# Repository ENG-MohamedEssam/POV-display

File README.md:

# POV-display
## Abstract
#### A POV (persistence of vision) display clock is a type of electronic display that uses LEDs to create the illusion of a moving image. In this case, it uses LEDs to represent an analog clock.

#### The system uses an Atmega32 microcontroller, which is a popular choice for embedded systems due to its low power consumption, high processing power and large number of I/O pins.

#### The driver code is responsible for controlling the LEDs, which are connected to the microcontroller's I/O pins. This code is responsible for turning the LEDs on and off at the appropriate times to create the illusion of a moving clock hand.

#### The algorithm is responsible for calculating the position of the clock hands based on the current time. It uses a combination of math and timing functions to determine the position of the hands and then sends the corresponding commands to the driver code to control the LEDs.

#### The project was developed by a team, and it's likely that the team divided the work and each member was responsible for a different part of the project. With this project, the team was able to demonstrate the ability to design and implement a complete embedded systems project, including writing code for both the microcontroller and the algorithm, as well as debugging and testing the system.

### The following is an image of the hardware system.

### You can find a preview of the project using the following link
[POV-Display-Preview](https://drive.google.com/drive/u/0/folders/128i1z9-Xx1qVnHIgvfxdt_CPARsultIw)

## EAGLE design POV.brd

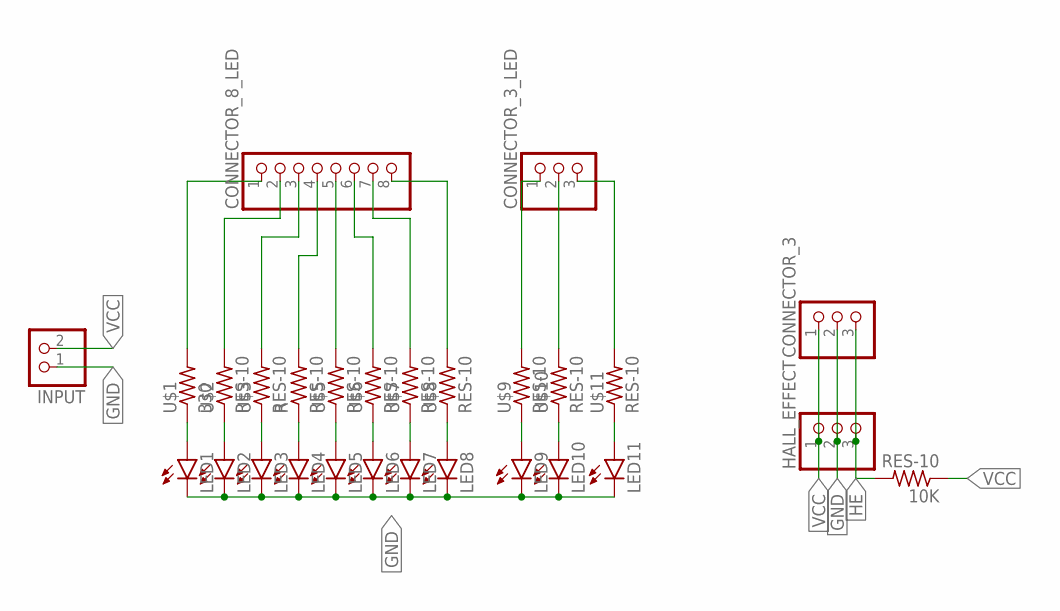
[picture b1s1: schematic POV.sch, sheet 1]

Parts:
10K: RES-10; 0207/10
CONNECTOR_3, CONNECTOR_3_LED: PINHD-1X3; 1X03
CONNECTOR_8_LED: PINHD-1X8; 1X08
HALL_EFFECT: PINHD-1X3; 1X03
INPUT: PINHD-1X2; 1X02
LED1, LED2, LED3, LED4, LED5, LED6, LED7, LED8, LED9, LED10, LED11: LED5MM
R: RES-10; 0207/10
U$1: 330; 0207/10
U$2, U$3, U$5, U$6, U$7, U$8, U$9, U$10, U$11: RES-10; 0207/10

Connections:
GND: CONNECTOR_3.2, HALL_EFFECT.2, INPUT.1, LED1.K (C), LED2.K (C), LED3.K (C), LED4.K (C), LED5.K (C), LED6.K (C), LED7.K (C), LED8.K (C), LED9.K (C), LED10.K (C), LED11.K (C); also elsewhere on the board
HE: 10K.2, CONNECTOR_3.3, HALL_EFFECT.3
unnamed: LED1.A, U$1.1
unnamed: LED2.A, U$2.1
unnamed: LED3.A, U$3.1
unnamed: LED4.A, R.1
unnamed: LED5.A, U$5.1
unnamed: LED6.A, U$6.1
unnamed: LED7.A, U$7.1
unnamed: LED8.A, U$8.1
unnamed: LED9.A, U$9.1
unnamed: LED10.A, U$10.1
unnamed: LED11.A, U$11.1
unnamed: CONNECTOR_8_LED.1, U$1.2
unnamed: CONNECTOR_8_LED.2, U$2.2
unnamed: CONNECTOR_8_LED.3, U$3.2
unnamed: CONNECTOR_8_LED.4, R.2
unnamed: CONNECTOR_8_LED.5, U$5.2
unnamed: CONNECTOR_8_LED.6, U$6.2
unnamed: CONNECTOR_8_LED.7, U$7.2
unnamed: CONNECTOR_8_LED.8, U$8.2
unnamed: CONNECTOR_3_LED.1, U$9.2
unnamed: CONNECTOR_3_LED.2, U$10.2
unnamed: CONNECTOR_3_LED.3, U$11.2
VCC: 10K.1, CONNECTOR_3.1, HALL_EFFECT.1, INPUT.2; also elsewhere on the board

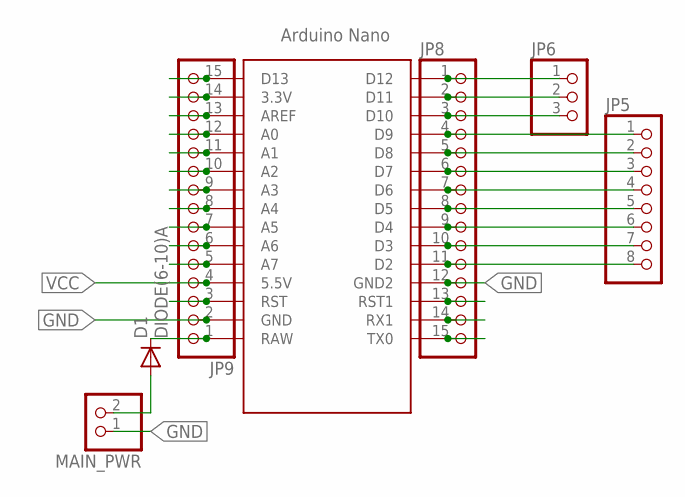
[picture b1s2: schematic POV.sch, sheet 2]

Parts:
D1: DIODE(6-10)A; DO201-15
JP5: PINHD-1X8; 1X08
JP6: PINHD-1X3; 1X03
JP8, JP9: PINHD-1X15; 1X15
MAIN_PWR: PINHD-1X2; 1X02
U$12: ARDUINO_NANO; NANO

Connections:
GND: JP8.12, JP9.2, MAIN_PWR.1, U$12.GND, U$12.GND1 (GND2); also elsewhere on the board
unnamed: JP9.14, U$12.3.3V
unnamed: JP9.13, U$12.AREF
unnamed: JP8.15, U$12.TX0
unnamed: JP8.14, U$12.RX1
unnamed: JP8.13, U$12.RST1
unnamed: JP5.8, JP8.11, U$12.D2
unnamed: JP5.7, JP8.10, U$12.D3
unnamed: JP5.6, JP8.9, U$12.D4
unnamed: JP5.5, JP8.8, U$12.D5
unnamed: JP5.4, JP8.7, U$12.D6
unnamed: JP5.3, JP8.6, U$12.D7
unnamed: JP5.2, JP8.5, U$12.D8
unnamed: JP5.1, JP8.4, U$12.D9
unnamed: D1.C, JP9.1, U$12.RAW
unnamed: D1.A, MAIN_PWR.2
unnamed: JP9.3, U$12.RST
unnamed: JP9.9, U$12.A3
unnamed: JP9.10, U$12.A2
unnamed: JP9.11, U$12.A1
unnamed: JP9.12, U$12.A0
unnamed: JP9.15, U$12.D13
unnamed: JP6.1, JP8.1, U$12.D12
unnamed: JP6.2, JP8.2, U$12.D11
unnamed: JP6.3, JP8.3, U$12.D10
unnamed: JP9.5, U$12.A7
unnamed: JP9.6, U$12.A6
unnamed: JP9.7, U$12.A5
unnamed: JP9.8, U$12.A4
VCC: JP9.4, U$12.5V (5.5V); also elsewhere on the board

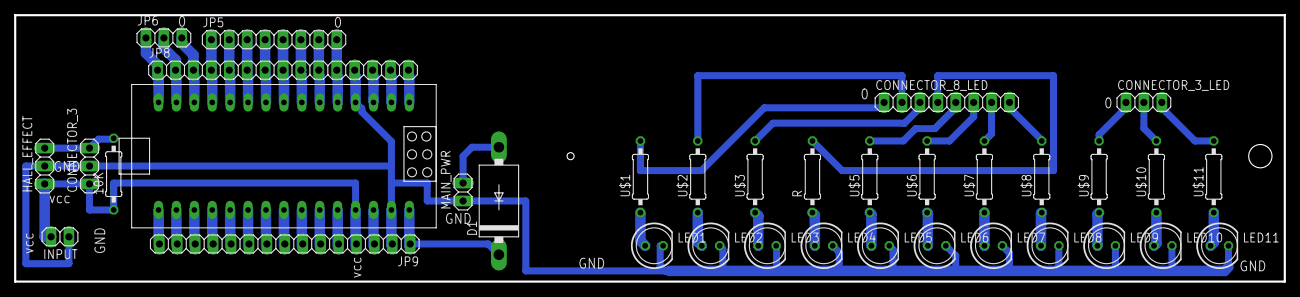
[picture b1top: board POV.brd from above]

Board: 2 copper layers, 180.0 x 37.8 mm, 35 parts (0 on the bottom side), 53 nets.

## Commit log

2022-12-11 Change in whole project
2022-12-17 added H.W board
2022-12-21 added sims
2023-01-13 final code
2023-01-13 adding image
2023-01-13 edit in readme
